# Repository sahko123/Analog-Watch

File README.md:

# Analog Watch

A watch that tells time using an analog voltmeter needle driven by a DAC. No screen. No hands. Just vibes and a carefully calibrated lookup table.

Featured in: **[I Built a Digital Watch With No Screen](https://youtu.be/faMIdIe0c6w)** (YOUTUBE LINK)

---

## What is this?

It's a watch. Technically. A Raspberry Pi Pico reads the time and drives an MCP4726 DAC, which pushes a voltage to a panel meter whose needle sweeps to represent whatever time-related concept you've most recently asked it about.

By default it shows seconds. Because why would you want to know the hours.

---

## How to read the time

Press a button.

| Button | Single Press | Double Click |
|--------|-------------|--------------|
| Top | Hours | Date |
| Mid | Month | Seconds |
| Low | Day of week | — |

The needle will swing to the correct position. Stare at it. Contemplate what you've built.

---

## Repo contents

| Path | What's in it |
|------|-------------|
| `ANALCLOCK_REV0_5.ino` | Arduino sketch (RP2040) |
| `analclock v1/` | KiCad PCB project — main board revisions 1 & 2 |
| `analclock v1/analog_dial/` | KiCad PCB project — the meter dial board |
| `analclock v1/gerberv1/` | Gerber files for the main board |
| `analclock v1/analog_dial/analogdial1gerbers/` | Gerber files for the dial board |
| `*.svg` / `*.dxf` | Watch face artwork |
| `*.step` / `*.stl` / `*.f3d` | 3D printed parts |

---

## Calibration

The meter needle is non-linear, so the firmware uses a cubic polynomial LUT to correct for this. You can tune it over serial:

```
dac <value>      — hold needle at a fixed DAC value
max <value>      — set full-scale and rebuild the LUT
set <idx> <val>  — manually poke a LUT entry
lut              — print current LUT
tz <offset>      — set UTC offset in hours
<unix timestamp> — set the time
```

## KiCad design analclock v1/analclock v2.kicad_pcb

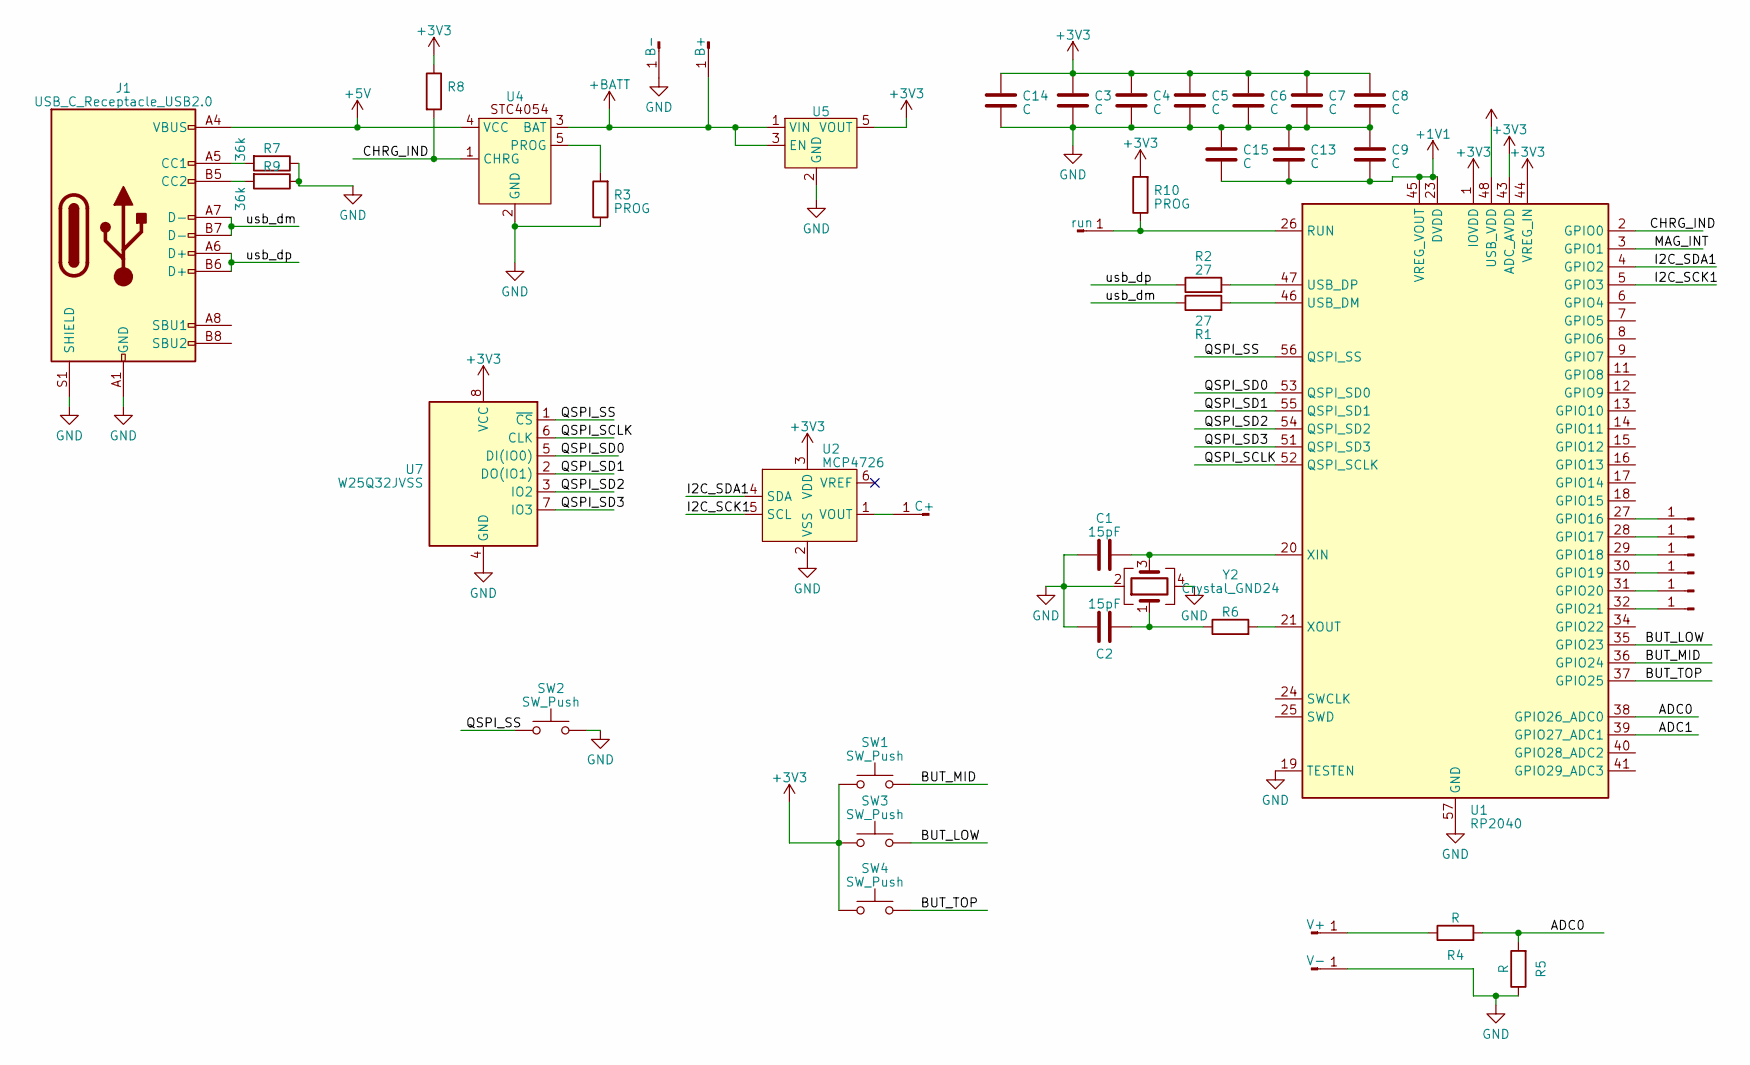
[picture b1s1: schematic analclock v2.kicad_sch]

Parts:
C1, C2: 15pF; C_0201_0603Metric_Pad0.64x0.40mm_HandSolder
C3, C4, C5, C6, C7, C13, C14, C15: C; C_0201_0603Metric_Pad0.64x0.40mm_HandSolder
C8, C9: C; C_0402_1005Metric
E1: B+; TestPoint_Pad_2.0x2.0mm
E2: B-; TestPoint_Pad_2.0x2.0mm
E3: C+; TestPoint_Pad_2.0x2.0mm
E4: V+; TestPoint_Pad_2.0x2.0mm
E5: V-; TestPoint_Pad_2.0x2.0mm
E6, E7, E8, E9, E10, E11: TestPoint_Pad_D1.0mm
E12: run; TestPoint_Pad_2.0x2.0mm
J1: USB_C_Receptacle_USB2.0; USB_C_Receptacle_GCT_USB4085
R1, R2: 27; R_0603_1608Metric_Pad0.98x0.95mm_HandSolder
R3, R10: PROG; R_0603_1608Metric_Pad0.98x0.95mm_HandSolder
R4, R5: R; R_0603_1608Metric
R6, R8: R_0402_1005Metric_Pad0.72x0.64mm_HandSolder
R7, R9: 36k; R_0402_1005Metric_Pad0.72x0.64mm_HandSolder
SW1, SW3, SW4: SW_Push; EVQP7A
SW2: SW_Push; PTS636
U1: RP2040; QFN-56-1EP_7x7mm_P0.4mm_EP3.2x3.2mm
U2: MCP4726; SOT-23-6
U4, U5: TSOT-23-5
U7: W25Q32JVSS; uson8
Y2: Crystal_GND24; Crystal_SMD_Abracon_ABM8G-4Pin_3.2x2.5mm

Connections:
+1V1: C9.2, C13.2, C15.2, U1.23 (DVDD), U1.45 (VREG_VOUT), U1.50 (DVDD)
+3V3: C3.1, C4.1, C5.1, C6.1, C7.1, C8.1, C14.1, R8.1, R10.2, SW1.1, SW3.1, SW4.1, U1.1 (IOVDD), U1.10 (IOVDD), U1.22 (IOVDD), U1.33 (IOVDD), U1.42 (IOVDD), U1.43 (ADC_AVDD), U1.44 (VREG_IN), U1.48 (USB_VDD), U1.49 (IOVDD), U2.3 (VDD), U5.5 (VOUT), U7.8 (VCC); also elsewhere on the board
+5V: J1.A4 (VBUS), J1.A9 (VBUS), J1.B4 (VBUS), J1.B9 (VBUS), U4.4 (VCC)
+BATT: E1.1, U4.3 (BAT), U5.1 (VIN), U5.3 (EN); also elsewhere on the board
/ADC0: R4.2, R5.2, U1.38 (GPIO26_ADC0)
/ADC1: U1.39 (GPIO27_ADC1)
/BUT_LOW: SW3.2, U1.35 (GPIO23)
/BUT_MID: SW1.2, U1.36 (GPIO24)
/BUT_TOP: SW4.2, U1.37 (GPIO25)
/CHRG_IND: R8.2, U1.2 (GPIO0), U4.1 (CHRG)
/I2C_SCK1: U1.5 (GPIO3), U2.5 (SCL); also elsewhere on the board
/I2C_SDA1: U1.4 (GPIO2), U2.4 (SDA); also elsewhere on the board
/MAG_INT: U1.3 (GPIO1); also elsewhere on the board
/QSPI_SCLK: U1.52 (QSPI_SCLK), U7.6 (CLK)
/QSPI_SD0: U1.53 (QSPI_SD0), U7.5 (DI(IO0))
/QSPI_SD1: U1.55 (QSPI_SD1), U7.2 (DO(IO1))
/QSPI_SD2: U1.54 (QSPI_SD2), U7.3 (IO2)
/QSPI_SD3: U1.51 (QSPI_SD3), U7.7 (IO3)
/QSPI_SS: SW2.1, U1.56 (QSPI_SS), U7.1 (~CS)
/usb_dm: J1.A7 (D-), J1.B7 (D-), R1.1
/usb_dp: J1.A6 (D+), J1.B6 (D+), R2.1
GND: C1.1, C2.1, C3.2, C4.2, C5.2, C6.2, C7.2, C8.2, C9.1, C13.1, C14.2, C15.1, E2.1, E5.1, J1.A1 (GND), J1.A12 (GND), J1.B1 (GND), J1.B12 (GND), J1.S1 (SHIELD), R3.1, R5.1, R7.1, R9.1, SW2.2, U1.19 (TESTEN), U1.57 (GND), U2.2 (VSS), U4.2 (GND), U5.2 (GND), U7.4 (GND), Y2.2, Y2.4; also elsewhere on the board
unnamed: C2.2, R6.1, Y2.1
unnamed: E3.1, U2.1 (VOUT)
unnamed: E4.1, R4.1
unnamed: E6.1, U1.32 (GPIO21)
unnamed: E7.1, U1.31 (GPIO20)
unnamed: E8.1, U1.30 (GPIO19)
unnamed: E9.1, U1.29 (GPIO18)
unnamed: E10.1, U1.28 (GPIO17)
unnamed: E11.1, U1.27 (GPIO16)
unnamed: E12.1, R10.1, U1.26 (RUN)
unnamed: J1.A5 (CC1), R7.2
unnamed: J1.B5 (CC2), R9.2
unnamed: R1.2, U1.46 (USB_DM)
unnamed: R2.2, U1.47 (USB_DP)
unnamed: C1.2, U1.20 (XIN), Y2.3
unnamed: R6.2, U1.21 (XOUT)
unnamed: R3.2, U4.5 (PROG)

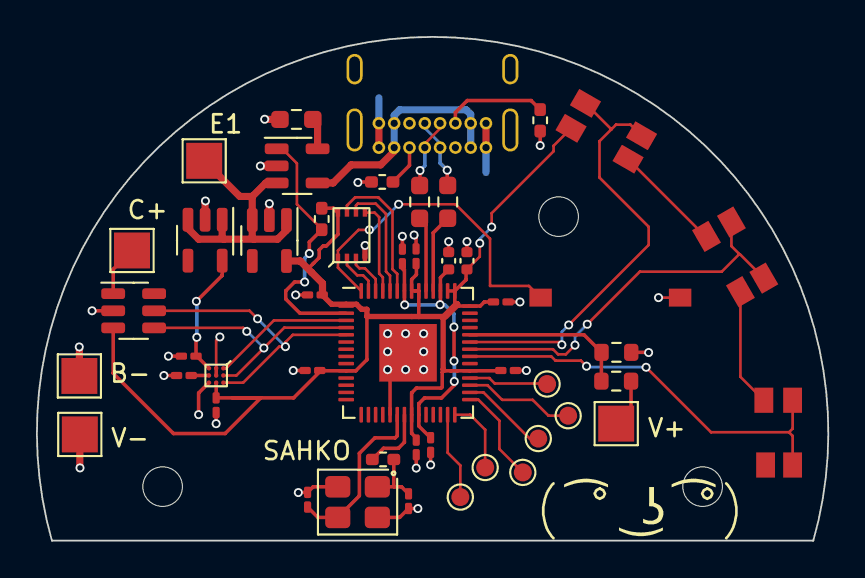
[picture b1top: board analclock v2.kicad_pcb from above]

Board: 2 copper layers, 44.0 x 28.0 mm, 48 parts (1 on the bottom side), 39 nets.

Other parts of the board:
C10, C11, C12: C; C_0201_0603Metric_Pad0.64x0.40mm_HandSolder
U3: BMM350
U6: TSOT-23-5

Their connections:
+1V8: C10.1, U3.C1 (VDD), U6.5 (VOUT)
+3V3: C11.1, U3.B3 (VDDIO); also elsewhere on the board
+BATT: U6.1 (VIN), U6.3 (EN); also elsewhere on the board
/I2C_SCK1: U3.A3 (SCK); also elsewhere on the board
/I2C_SDA1: U3.A2 (SDA); also elsewhere on the board
/MAG_INT: U3.A1 (INT); also elsewhere on the board
GND: C10.2, C11.2, C12.1, U3.B1 (GND), U3.B2 (ADSEL), U3.C3 (BYPASS), U6.2 (GND); also elsewhere on the board
unnamed: C12.2, U3.C2 (CRST)

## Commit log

2026-05-23 Initial commit: ANALCLOCK_REV0_5 Arduino sketch and design files
2026-05-23 Add README
